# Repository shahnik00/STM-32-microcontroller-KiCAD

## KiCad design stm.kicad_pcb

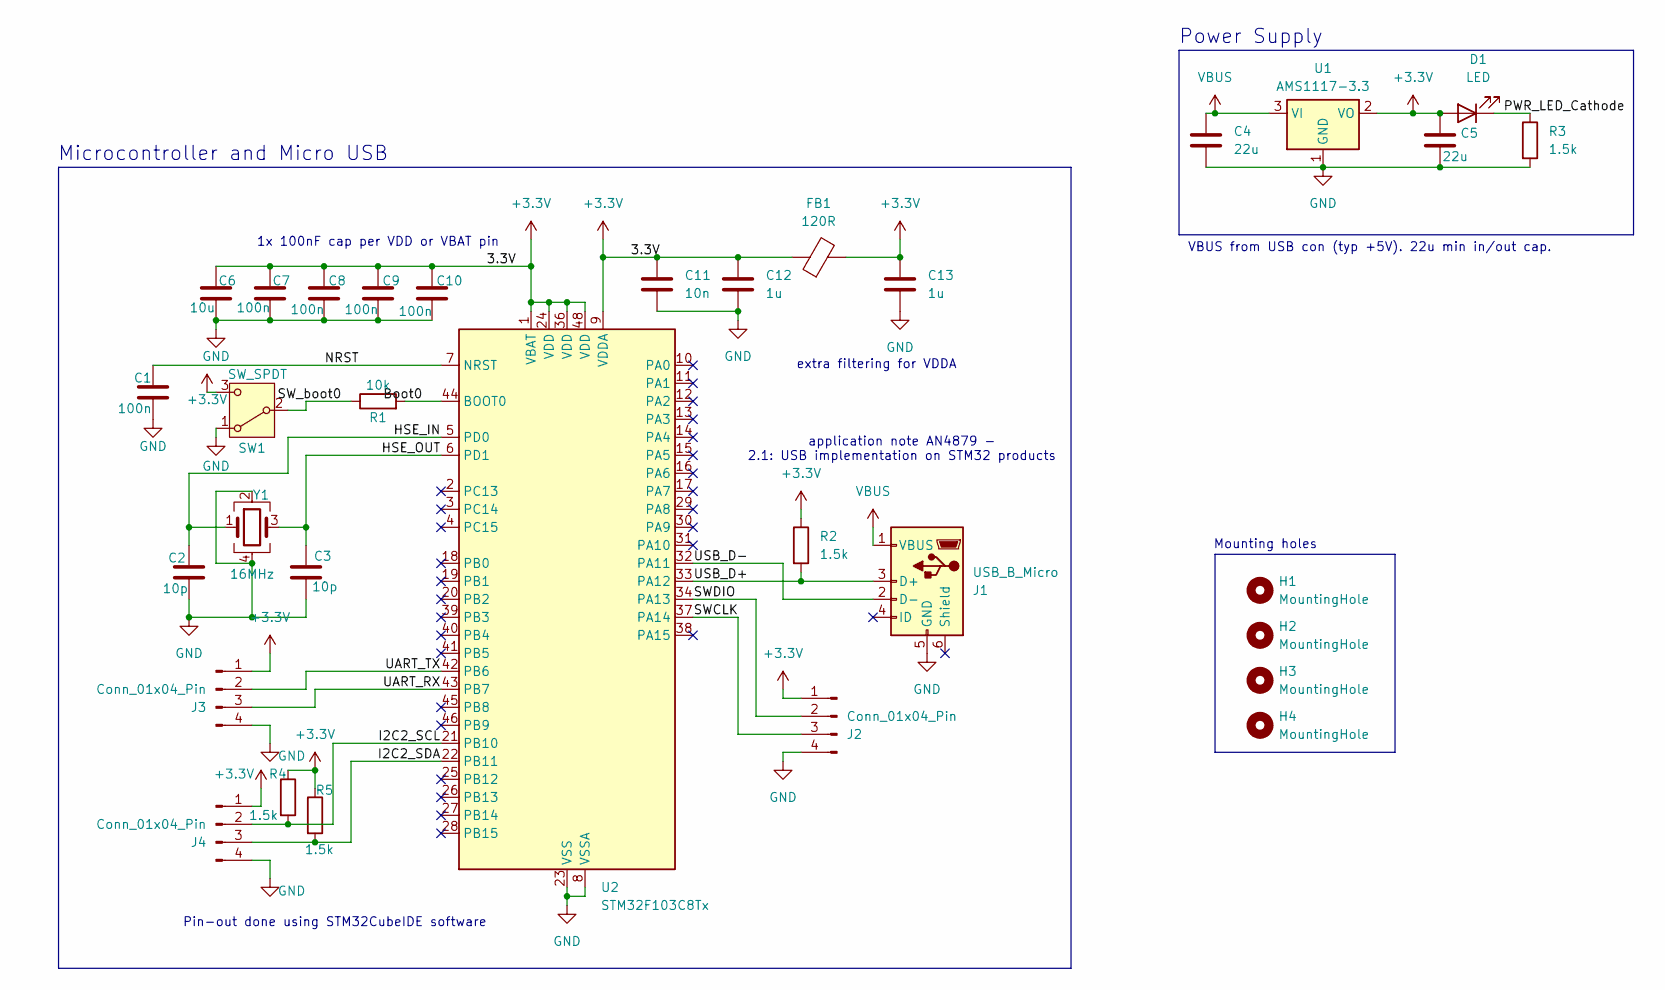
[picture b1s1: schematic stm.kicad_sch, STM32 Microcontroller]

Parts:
C1, C7, C8, C9, C10: 100n; C_0402_1005Metric_Pad0.74x0.62mm_HandSolder
C2, C3: 10p; C_0402_1005Metric_Pad0.74x0.62mm_HandSolder
C4, C5: 22u; C_0805_2012Metric_Pad1.18x1.45mm_HandSolder
C6: 10u; C_0603_1608Metric_Pad1.08x0.95mm_HandSolder
C11: 10n; C_0402_1005Metric_Pad0.74x0.62mm_HandSolder
C12, C13: 1u; C_0402_1005Metric_Pad0.74x0.62mm_HandSolder
D1: LED; LED_0805_2012Metric_Pad1.15x1.40mm_HandSolder
FB1: 120R; L_0603_1608Metric_Pad1.05x0.95mm_HandSolder
H1, H2, H3, H4: MountingHole; MountingHole_2.1mm
J1: USB_B_Micro; USB_Micro-B_Molex_47346-0001
J2, J3, J4: Conn_01x04_Pin; PinHeader_1x04_P2.54mm_Vertical
R1: 10k; R_0402_1005Metric_Pad0.72x0.64mm_HandSolder
R2, R3, R4, R5: 1.5k; R_0402_1005Metric_Pad0.72x0.64mm_HandSolder
SW1: SW_SPDT; SW_SPST_B3U-1100P-B
U1: AMS1117-3.3; SOT-223-3_TabPin2
U2: STM32F103C8Tx; LQFP-48_7x7mm_P0.5mm
Y1: 16MHz; Crystal_SMD_3225-4Pin_3.2x2.5mm_HandSoldering

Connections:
+3.3V: C5.1, C6.1, C7.1, C8.1, C9.1, C10.1, C11.1, C12.1, C13.1, D1.2 (A), FB1.1, FB1.2, J2.1, J3.1, J4.1, R2.1, R4.1, R5.1, SW1.3 (C), U1.2 (VO), U2.1 (VBAT), U2.9 (VDDA), U2.24 (VDD), U2.36 (VDD), U2.48 (VDD)
/Boot0: R1.2, U2.44 (BOOT0)
/HSE_IN: C2.1, U2.5 (PD0), Y1.1
/HSE_OUT: C3.1, U2.6 (PD1), Y1.3
/I2C2_SCL: J4.2, R4.2, U2.21 (PB10)
/I2C2_SDA: J4.3, R5.2, U2.22 (PB11)
/NRST: C1.2, U2.7 (NRST)
/PWR_LED_Cathode: D1.1 (K), R3.1
/SWCLK: J2.3, U2.37 (PA14)
/SWDIO: J2.2, U2.34 (PA13)
/SW_boot0: R1.1, SW1.2 (B)
/UART_RX: J3.3, U2.43 (PB7)
/UART_TX: J3.2, U2.42 (PB6)
/USB_D+: J1.3 (D+), R2.2, U2.33 (PA12)
/USB_D-: J1.2 (D-), U2.32 (PA11)
GND: C1.1, C2.2, C3.2, C4.2, C5.2, C6.2, C7.2, C8.2, C9.2, C10.2, C11.2, C12.2, C13.2, J1.5 (GND), J2.4, J3.4, J4.4, R3.2, SW1.1 (A), U1.1 (GND), U2.8 (VSSA), U2.23 (VSS), U2.35 (VSS), U2.47 (VSS), Y1.2, Y1.4
VBUS: C4.1, J1.1 (VBUS), U1.3 (VI)

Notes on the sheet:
Pin-out done using STM32CubeIDE software
application note AN4879 - 2.1: USB implementation on STM32 products
Microcontroller and Micro USB
extra filtering for VDDA
1x 100nF cap per VDD or VBAT pin
Power Supply
Mounting holes
VBUS from USB con (typ +5V). 22u min in/out cap.

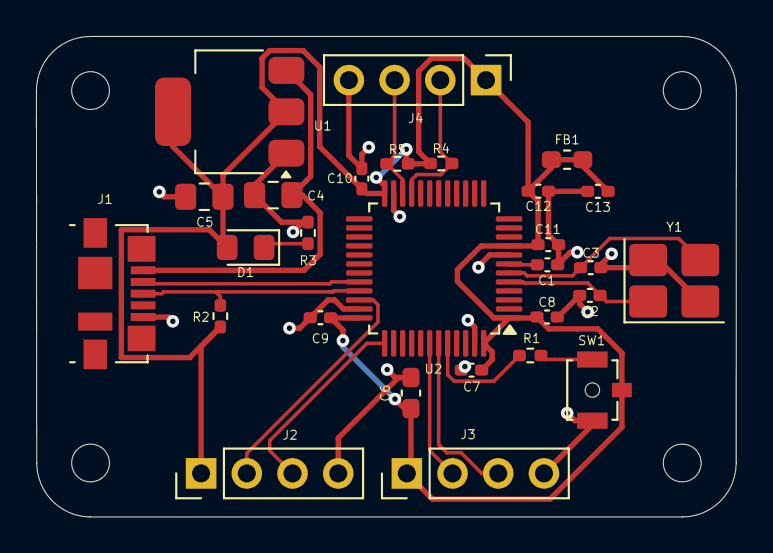
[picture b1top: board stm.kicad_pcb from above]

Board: 2 copper layers, 38.9 x 26.7 mm, 32 parts (0 on the bottom side), 17 nets.
